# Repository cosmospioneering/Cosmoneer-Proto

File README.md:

#Cosmos Pioneering   -   Cosmoneer Proto#
==========================================

The Cosmoneer Proto is a single-degree of Freedom Spacecraft simulator.  This design is the main control board to manage the attitude in a single axis via PWM control through a server and gyro motor, commonly known as a Control Moment Gyro.

----------

# CONTENTS #

This repository contains source files for the Cosmoneer Proto.  Here is a table of contents for the repository.

- 3DModels: Rhino 3.0 models, with a sub folder containing Rhino output STL files
- Arduino: Arduino code in two folders, with additional required libraries contained in a separate zip file.
- Rev0-fab: Rev 0 PCB fabrication files (copper, mask, silk, drill, dwg)
- SpecSheets: Manufacturing spec sheets for components used on the Cosmoneer Proto circuit board
- fab: Rev 01 PCB fabrication files (copper, mask, silk, drill, dwg)
- boards: [KiCAD](http://www.kicad-pcb.org/display/KICAD/KiCad+EDA+Software+Suite) PCB board files (CosmoneerProto, SuperBurst & Serial IrDa)

# LICENSE #

*This project is open source hardware as defined by the* [Open Source Hardware (OSHW) Definition 1.0](http://freedomdefined.org/OSHW)
- Documentation under the following license:  [Creative Commons Attribution-ShareAlike 4.0 Unported License](http://creativecommons.org/licenses/by-sa/4.0/)
- Source code is under the following license:  [GNU General Public License, version 3 (GPL-3.0)](https://opensource.org/licenses/GPL-3.0)

[![alt][2]][1] [![alt][4]][3] [![alt][6]][5]

[1]: http://creativecommons.org/licenses/by-sa/4.0/
[2]: http://i.creativecommons.org/l/by-sa/4.0/88x31.png (Creative Commons Attribution-ShareAlike 4.0 Unported License.)

[3]: http://freedomdefined.org/OSHW
[4]: http://www.oshwa.org/wp-content/uploads/2014/03/oshw-logo-antipixel.png

[5]: https://opensource.org/licenses/GPL-3.0
[6]: https://www.gnu.org/graphics/gplv3-88x31.png

----------

# Disclaimer #

THE CONTENT OF THIS FOLDER IS PROVIDED "AS IS" AND "WITH ALL FAULTS". Cosmos Pioneering DISCLAIMS ALL OTHER WARRANTIES, EXPRESS OR IMPLIED, REGARDING PRODUCTS, INCLUDING BUT NOT LIMITED TO, ANY IMPLIED WARRANTIES OF MERCHANTABILITY OR FITNESS FOR A PARTICULAR PURPOSE.

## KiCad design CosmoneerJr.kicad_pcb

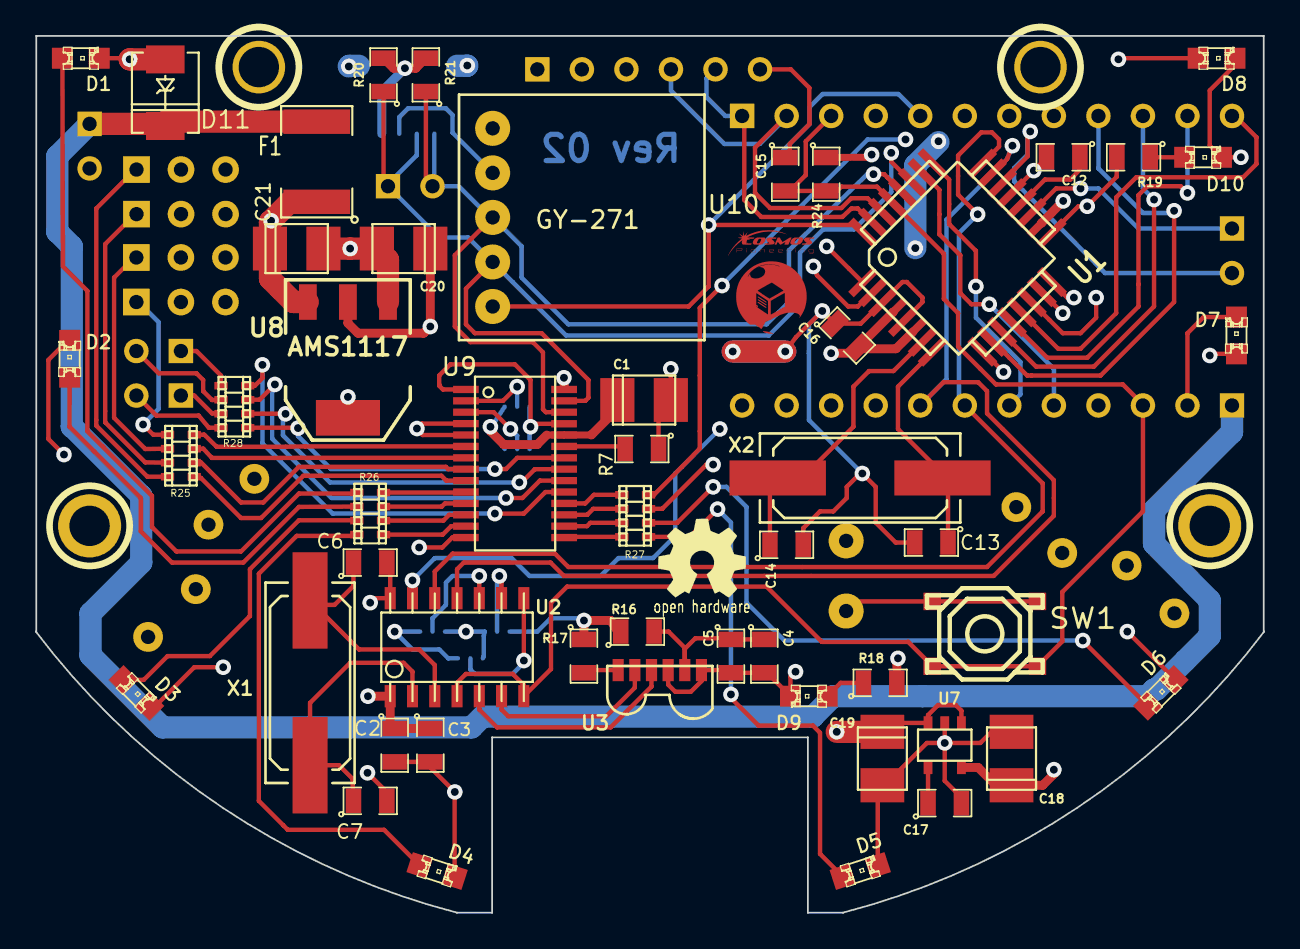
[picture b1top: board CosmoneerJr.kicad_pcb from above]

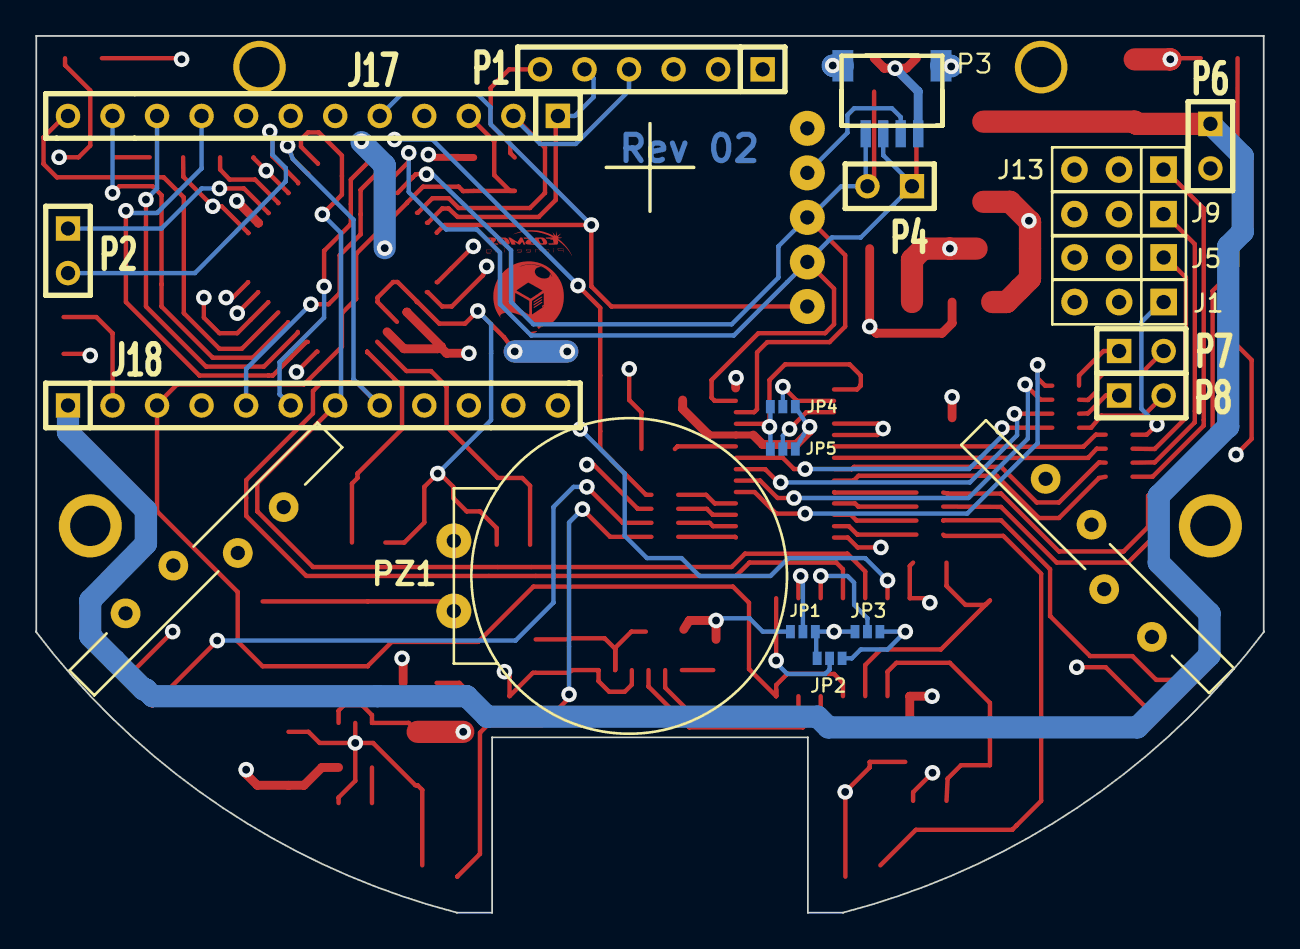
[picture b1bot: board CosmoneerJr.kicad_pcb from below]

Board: 4 copper layers, 70.0 x 50.0 mm, 77 parts (21 on the bottom side), 78 nets.

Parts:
1PIN, 1PIN#2, 1PIN#3, 1PIN#4: P***; Mhole
C1, C18, C19, C20, C21: 10uf; c_tant_B
C2, C4: 4.7uf; SM0805
C3, C5, C12, C15, C16, C17: 0.1uf; SM0805
C6, C7: 27pf; SM0805
C13, C14: 15pf; SM0805
D1, D2, D3, D4, D5, D6, D7, D8, D9, D10: LED; LED-0805
D11: 1N4001; DO-214AC(SMA)
F1: FUSE; SM1812
GY-271: U10; GY-271
J1, J5, J9, J13: Header; PIN_ARRAY_3X1
J17, J18: Header; SIL-12
JP1, JP2, JP3, JP4, JP5: JUMPER3; S_JUMPER_3
P1: .1" Header; SIL-6
P2, P4, P6: Header; SIL-2
P3: SM04B-SRSS-TB; con-jst2-SM04B-SRSS-TB
P7, P8: CONN_2; SIL-2
PZ1: PIEZO Speaker; piezo_spkr
PressFitPCB: VAL**; PressFitPCB
PressFitPCB#2: VAL**; PressFitPCB
R7, R20, R21, R24: 10K; SM0805
R16: 47 Ohm; SM0805
R17: 0 Ohm; SM0805
R18, R19: 1K; SM0805
R25, R26, R27, R28: 330 Ohm; r_cat16-4
SW1: SW_PUSH_SMALL; smd_push2
U1: ATMEGA328P-AU; TQFP32
U2: MCP2120-SL; so-14
U3: TFBS4711; vishay_TFBS4711
U7: MIC5205; SOT23-5
U8: AMS1117; SOT223
U9: PCA9685
VAL: REF; LOGO
X1: 7.3728Mhz; Q_49U3HMS
X2: 16.000Mhz; Q_49U3HMS

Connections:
+5V: C1.1, C2.1, C3.1, C16.2, C18.1, C20.1, GY-271.1, J18.4, JP1.3, JP2.3, JP3.3, JP4.3, JP5.3, P1.3, P3.1, R16.1, R17.1, R18.2, R20.2, R21.2, R24.1, U1.4, U1.6, U1.18, U2.1, U7.5, U8.2, U8.4, U9.4, U9.5, U9.24, U9.28
/A0: J18.8, U1.23, U2.11
/A1: J18.7, U1.24, U2.12
/A2: J18.6, U1.25
/A3: J18.5, U1.26
/A6: P2.1, U1.19
/A7: P2.2, U1.22
/D3: J17.6, U1.1
/D6: J17.9, U1.10
/D7: J17.10, U1.11
/D9: J17.12, U1.13
/D10: J18.12, U1.14
/D12: J18.10, U1.16
/DTR: C15.1, P1.6
/I2C_SCL_5V: GY-271.3, P3.4, P4.2, R21.1, U1.28, U9.26
/I2C_SDA_5V: GY-271.4, P3.3, P4.1, R20.1, U1.27, U9.27
/INT: GY-271.5, J17.5, U1.32
/LED_Data: J18.11, U1.15
/LED_RegClk: J17.11, U1.12
/LED_SerClk: J18.9, R19.2, U1.17
/MOTOR1_PWM: R25.7, U9.7
/MOTOR2_PWM: R25.5, U9.9
/MOTOR3_PWM: R28.7, U9.20
/MOTOR4_PWM: R28.5, U9.22
/PIEZO: J17.7, PZ1.2, U1.2
/PWMSPARE1: R26.8, U9.10
/PWMSPARE2: R26.7, U9.11
/PWMSPARE3: R26.6, U9.12
/PWMSPARE4: R26.5, U9.13
/PWMSPARE5: R27.8, U9.15
/PWMSPARE6: R27.7, U9.16
/PWMSPARE7: R27.6, U9.17
/PWMSPARE8: R27.5, U9.18
/RA1: JP4.2, U9.2
/RA2: JP5.2, U9.3
/RAW: D11.2, F1.2, J18.1, P6.1
/RESET: C15.2, J17.3, J18.3, R24.2, SW1.1, SW1.4, U1.29, U2.4, U2.7
/RXI: J17.2, P1.4, U1.30
/SERVO1_PWM: R25.8, U9.6
/SERVO2_PWM: R25.6, U9.8
/SERVO3_PWM: R28.8, U9.19
/SERVO4_PWM: R28.6, U9.21
/TXO: J17.1, P1.5, U1.31
ENABLE: J17.8, U1.9, U2.13
GND: 1PIN#3.1, C1.2, C2.2, C3.2, C4.2, C5.2, C6.2, C7.2, C12.2, C13.2, C14.2, C16.1, C17.2, C18.2, C19.2, C20.2, C21.2, D1.2, D2.2, D3.2, D4.2, D5.2, D6.2, D7.2, D8.2, D9.2, D10.2, D11.1, GY-271.2, J1.3, J5.3, J9.3, J13.3, J17.4, J18.2, JP1.1, JP2.1, JP3.1, JP4.1, JP5.1, P1.1, P1.2, P3.2, P3.FIT@, P6.2, PZ1.1, R7.1, SW1.2, SW1.3, U1.3, U1.5, U1.21, U2.14, U3.4, U3.6, U7.2, U8.1, U9.1, U9.14, U9.25
unnamed: JP3.2, U2.10
unnamed: C12.1, U1.20
unnamed: U2.5, U3.3
unnamed: U2.6, U3.2
unnamed: C4.1, C5.1, R16.2, U3.5
unnamed: JP2.2, U2.8
unnamed: JP1.2, U2.9
unnamed: D10.1, R19.1
unnamed: C17.1, U7.4
unnamed: D9.1, R18.1
unnamed: C14.1, U1.7, X2.1
unnamed: C13.1, U1.8, X2.2
unnamed: R7.2, U9.23
unnamed: P8.1, R28.3
unnamed: P8.2, R28.4
unnamed: P7.1, R28.1
unnamed: P7.2, R28.2
unnamed: J13.1, R25.4
unnamed: J1.1, R25.1
unnamed: J5.1, R25.2
unnamed: J9.1, R25.3
unnamed: D6.1, R27.2
unnamed: D1.1, R26.1
unnamed: D2.1, R26.2
unnamed: D3.1, R26.3
unnamed: D4.1, R26.4
unnamed: D5.1, R27.1
unnamed: D7.1, R27.3
unnamed: D8.1, R27.4
unnamed: R17.2, U3.1
unnamed: C7.1, U2.2, X1.1
unnamed: C6.1, U2.3, X1.2
VCC: C19.1, C21.1, F1.1, J1.2, J5.2, J9.2, J13.2, U7.1, U7.3, U8.3

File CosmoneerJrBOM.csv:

"Id";"Designator";"Package";"Quantity";"Designation";"Supplier and ref";
1;"U3";"vishay_TFBS4711";1;"TFBS4711";;;
2;"U1";"TQFP32";1;"ATMEGA328P-AU";;;
3;"SW1";"SW_PUSH_SMD";1;"SW_PUSH_SMALL";;;
4;"U7";"SOT23-5";1;"MIC5205";;;
5;"U8";"SOT223";1;"AMS1117";;;
6;"U2";"so-14";1;"MCP2120-SL";;;
7;"C15,C12,C11,C10,C17,C16,C3,C5";"SM0805";8;"0.1uf";;;
8;"R24,R22,R23,R20,R21,R7";"SM0805";6;"10K";;;
9;"R19,R18";"SM0805";2;"1K";;;
10;"C7,C14,C13,C6";"SM0805";4;"22pf";;;
11;"C8,C2,C4";"SM0805";3;"4.7uf";;;
12;"C9";"SM0805";1;"0.22uf";;;
13;"R17";"SM0805";1;"0 Ohm";;;
14;"R16";"SM0805";1;"47 Ohm";;;
15;"P1";"SIL-6";1;".1in Header";;;
16;"P2,P5,P4,P6";"SIL-2";4;"Header";;;
17;"J17,J18";"SIL-12";2;"Header";;;
18;"JP1,JP3,JP2,JP4,JP5";"S_JUMPER_3";5;"JUMPER3";;;
19;"R25,R28";"r_CN2A4";2;"220 Ohm";;;
20;"R26,R27";"r_CN2A4";2;"330 Ohm";;;
21;"X2";"Q_49U3HMS";1;"16.000Mhz";;;
22;"X1";"Q_49U3HMS";1;"7.3728Mhz";;;
23;"J5,J1,J9,J13";"PIN_ARRAY_3X1";4;"Header";;;
24;"PZ1";"piezo_spkr";1;"PIEZO Speaker";;;
25;"U4";"pca9306dcu";1;"PCA9306";;;
26;"D10,D9,D7,D8,D4,D6,D1,D2,D3,D5";"LED-0805";10;"LED";;;
27;"U5";"HMC5883L_bigpads";1;"HMC5883";;;
28;"P3";"con-jst2-SM04B-SRSS-TB";1;"SM04B-SRSS-TB";;;
29;"C18,C1,C20,C21,C19";"c_tant_B";5;"10uf";;;
30;"U9";"PCA9685";1;"PCA9685";;;
31;"P7,P8";"SIL-2";2;"CONN_2";;;
32;"1PIN,1PIN,1PIN,1PIN";"Mhole";4;"P***";;;
33;"PressFitPCB,PressFitPCB";"PressFitPCB";2;"VAL**";;;
34;"G***";"Logo_silk_OSHW_6x6mm";1;"LOGO";;;
35;"VAL";"LOGO";1;"REF";;;

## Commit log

2014-06-28 Initial Commit
    This is the initial Comoneer Junior design. Expect some changes in the
    future. Will publish the source code in a separate repository.
2014-06-28 Fixed Readme
    Minor ReadMe changes
2014-07-01 PDF added
    Generated a pdf version of the schematic
    Schematic fixes made
    Net connections on U1 were disconnected during component move. Nets
    reconnected, pdf generated, netlist generated and re-imported into pcb.
    PCB file updated and saved.
2014-11-14 Pressfit PCB additions
    Added pads, drills and Silkscreen outlines for press fit pcb additions.
2015-01-01 Moved parts and run lines
    Moved several parts and began running traces. Added two additional
    internal layers, bringing the board to a total of four layers.
2015-02-12 new changes
    More routing and parts movement
2015-02-13 Final changes
2015-02-15 Final changes
    Re-added mounting holes and migrated pressFit silk screen to back side
    of PCB
2015-02-17 Rev Zero Prototype
    Silkscreen cleanup, minor part movements
2015-02-17 Generated PCB Fabrication Files
    Generated and edited pcb files. Made a couple of minor cleanup fixes to
    inner copper layer 2.
2015-02-19 Rev Zero Cleanup
    Eliminated vias and extra verticies in traces. Prepared bottom
    silkscreen to merge with bottom layer.
2015-07-26 Rev ZeroOne Prototype
    Parts added, Schematic updated and PCB updated and Mfg files generated
2015-09-19 Rev 02
    Fixes made to PCB for Rev 02. Additional files for Rev 01/02 design
    added to repository.
2015-11-17 Compass Self-Cal
    Compass self calibration code implemented. Lower speed setup for ESC &
    gyro motor. Compass point headings are now sought out by the Cosmoneer.
    End user may need to comment out the current sensor code (INA219 library
    reference).
2016-09-30 IrDa and SuperBurst Additions
    Additions and changes to projects
2016-10-30 Add files via upload
    Added readme for clarity
2017-05-24 Evolution 18.2 update
    Added Serial IrDa detection routine. Updated code to support latest
    version of the Digole OLED display. Added zip files for libraries to
    18.2 folder.
2017-06-26 OLED & Compass Updates
    Removed timers in favor of constant maneuverung calls via main loop.
    Compass smoothing function was reworked. OLED display updates and
    library updates made. Changes made to support Arduino interface version
    1.6.10.
2017-07-17 PID Loop timing changes
    Changes made to the PID loop to remove "delay" programming. Counters
    introduced to trigger events after so many loops, as the refresh rate
    was too high for some events and the devices attempting to be refreshed.
2018-02-23 Evo 18.5 Upload
    Reverted back to 16.8 target selection code and 16.8 setServo subroutine
    usage. Fixed logo display issue on startup, as well as moved and
    modified the servo centering step, so it centered the servo and then
    released the servo. This resulted in a reduction of current draw by the
    servo during motor startup. Once started, the servo could be re-engaged
    from the "center" position. This code also uses the GY-86 board, which
2018-02-23 Quick Start Guide
    Added the Quick Start Guide for 18.5
